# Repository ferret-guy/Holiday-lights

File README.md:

Holiday-Magic-Lights code

All recent developments are in ./HolidayLights/led_ir

Developed on Aquino IDE 1.05 and Arduino IDE 1.5.6r2

Todo:
    Add Basic Animations
        Scrolling
        Twinkling
        Rainbow
    Add more colors
	Add IR capability
	Fix even-number separation modes

NOTES:
Writing to strip of 144 length is 1.25ms
Writing to strip of 045 length is 1.35ms (what?)
Writing to strip of 189 length is 1.58ms
Writing to strip of 300 length is 1.85ms (specified maximum)

MODES:
0 - Off
1 - Separation Mode (Including Chaser Mode)
2 - Solid Mode
3 - Rainbow Mode
4 - Blink Mode
5 - Twinkle Mode

SPECIAL CONTROLS:
Special features activated through mode button (5th row, 2nd column):

1.
In Separation Mode, Switches through seperation modes (Starts at 1, goes to 2, then 3, then 0, then 1 again)
Mode number is now many times each color occurs.
!! Separation mode 0 is chaser mode. !!

2.
In Solid Mode, cycles through preset strip lengths. IN DEVELOPMENT FIRMWARE, THIS IS:
	45 long, 144 long, 189 long, then 45 long again.
THIS WILL BE CHANGED TO INTERVALS OF 60 FOR PRODUCTION?

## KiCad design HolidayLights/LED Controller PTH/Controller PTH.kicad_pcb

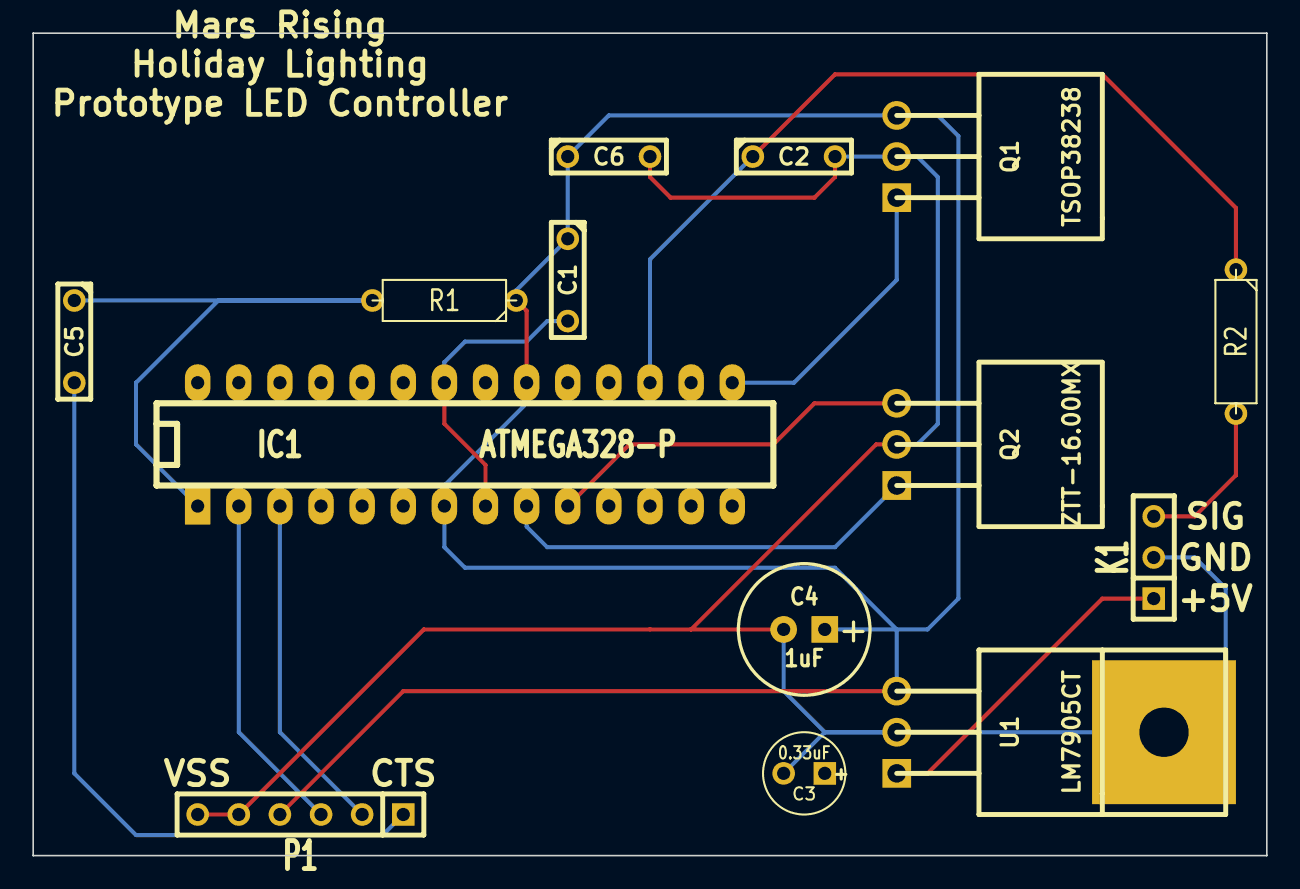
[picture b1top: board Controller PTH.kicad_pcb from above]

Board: 2 copper layers, 76.2 x 50.8 mm, 14 parts (0 on the bottom side), 13 nets.

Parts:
C1, C2, C5, C6: 0.1uF; C2
C3: 0.33uF; C1V5
C4: 1uF; C1V8
IC1: ATMEGA328-P; DIP-28__300_ELL
K1: CONN_3; SIL-3
P1: CONN_6; SIL-6
Q1: TSOP38238; TO220
Q2: ZTT-16.00MX; TO220
R1: 10K; R3-5
R2: 300; R3-5
U1: LM7905CT; TO220

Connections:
unnamed: C5.1, IC1.1, R1.2
unnamed: IC1.3, P1.2
unnamed: C5.2, P1.1
unnamed: K1.3, R2.2
unnamed: IC1.15, Q1.1
unnamed: C2.1, IC1.17, R2.1
unnamed: C1.2, IC1.8, IC1.22
unnamed: IC1.9, Q2.1
unnamed: IC1.10, Q2.3
unnamed: IC1.2, P1.3
VCC: C1.1, C4.1, C6.1, IC1.7, IC1.20, P1.4, Q1.3, R1.1, U1.3
VPP: C3.1, K1.1, U1.1
VSS: C2.2, C3.2, C4.2, C6.2, K1.2, P1.5, P1.6, Q1.2, Q2.2, U1.2

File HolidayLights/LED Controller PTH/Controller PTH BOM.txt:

╔═════════════════════════════════════════════════╗
   ║LED Controller PTH Prototype -- Bill of Materials║
╔══╩════════════╦═══════╦═══════════════════╦════════╩══╗
║ Component     ║ Name  ║ Digikey P/N       ║ Price     ║
╠═══════════════╬═══════╬═══════════════════╬═══════════╣
║ 0.1uF         ║ C1    ║ 399-9845-ND       ║ $0.45     ║
║ 0.1uF         ║ C2    ║ 399-9845-ND       ║ $0.45     ║
║ 0.1uF         ║ C5    ║ 399-9845-ND       ║ $0.45     ║
║ 0.1uF         ║ C6    ║ 399-9845-ND       ║ $0.45     ║
║ 0.33uF        ║ C3    ║ 493-12794-1-ND    ║ $0.17     ║
║ 1uF           ║ C4    ║ UKL1H010KDDANA-ND ║ $0.42     ║
║ ATMEGA328-P   ║ IC1   ║ ATMEGA328-PU-ND   ║ $3.41     ║
║ CONN_3        ║ K1    ║ 5-826951-0-ND     ║ $0.20*    ║
║ CONN_6        ║ P1    ║ 5-826951-0-ND     ║ $0.40*    ║
║ TSOP38238     ║ Q1    ║ 751-1227-ND       ║ $1.12     ║
║ ZTT-16.00MX   ║ Q2    ║ X908-ND           ║ $0.70     ║
║ 300           ║ R2    ║ CF14JT300RCT-ND   ║ $0.08     ║
║ 10K           ║ R1    ║ CF14JT10K0CT-ND   ║ $0.08     ║
║ LM7905CT      ║ U1    ║ NCP7805TGOS-ND    ║ $0.46     ║
╠═══════════════╬═══════╬═══════════════════╬═══════════╣
║ TOTAL COST    ║░░░░░░░║░░░░░░░░░░░░░░░░░░░║ $11.54    ║
╠═══════════════╩═══════╩═══════════════════╩═══════════╣
║*Calculated from total cost of 50-position breakaway.  ║
║ Total cost is increased due to this.                  ║
╚═══════════════════════════════════════════════════════╝

201 205 203 205 187 ╔═╦═╗
186 176 186 177 186 ║░║▒║
204 205 206 205 185 ╠═╬═╣
186 178 186 219 186 ║▓║█║
200 205 202 205 188 ╚═╩═╝

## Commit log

2014-05-20 Added Basic LED handeling
    Added basic color traking and color handeling
2014-05-20 Added Readme
2014-05-20 Changed Readme format
2014-05-20 Wrapped up extra color
    Extra color is now off
2014-05-20 Added adafruit ir example code
    https://learn.adafruit.com/ir-sensor/reading-ir-commands
2014-05-22 Experemintal low ram LED
2014-05-29 Fixed odd port on arduino mini
    (bus D, pin 7 bit 7)
2014-05-29 Bentchmark
    Bentchmark shows infanate sin
2014-05-29 Minir changes
2014-05-29 no need to commit this
2014-05-29 Lots f code reform
2014-05-30 changes color seprration moder
2014-05-30 Demo strip brightness
2014-05-30 New techniques
2014-06-01 Total rewrite, PC control, and controller pcb.
    Created windows app and supporting controller firmware for testing and
    development.
    Completely rewrote controller firmware for improved rendering and PC
    control support.
    Created prototype Part-Through-Hole controller PCB.
    All new items are in ./HolidayLights
2014-06-01 LED Control Utility Quickfix
    A block of code used for debugging was left turned on, which created a
    large lag time.
2014-06-02 Minor app update, major firmware update
    Added updating color presets to serial control.
    Completely and fully finished color separation mode.
2014-06-05 stuff
2014-06-06 Many changes to serial control
    Added remote function (kinda works some locking)
2014-06-06 Little work on 1 byte (not at all working)
2014-06-09 Remote Emulation and Serial Restructure
    Serial communication between PC and Arduino restructured to be variable
    byte length, increasing reliability and flexibility.
    Remote Emulator utility brought to full functionality, as well as
    remote-control functions in the firmware. Additionally, the firmware now
    processes relevant commands while color separation mode is running.
2014-06-09 Color Enabling Quickfix
    Minimum colors enabled limited to 2, as one or zero breaks everything
    until the controller is reset.
2015-01-31 IR is starting to happen... again.
    Documented the IR codes from the remotes and began converting current
    firmware to IR operation.
2015-01-31 Infrared is fully functional
    Also implemented the solid color button, switching modes, etc. and
    changed the old firmware slightly to work with the new dev board. Tester
    firmware also included.
2015-03-07 All kinds of overhaul
    Added rainbow mode, twinkle mode, blink mode, reversing, mode
    infrastructure, IR optimizations, strip length changing, event handlers,
    and probably some other stuff.
2015-03-15 Speed changes and pin changes
    Now starts off on separation mode with only white enabled and at zero
    speed. Also, chaser mode is fixed. Pins have been changed for actual
    platform.
2015-03-15 Refix
    Actually start out in mode one.
2015-03-15 Revert "Refix"
    This reverts commit a0446dbd24dc509682fc70a8322280eecec5673b.
2015-03-15 Revert "Revert "Refix""
    This reverts commit 542e6cbcefcfbbfaa3922c073ab42bb967258520.
